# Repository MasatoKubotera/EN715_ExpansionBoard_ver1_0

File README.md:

<html lang="en">
  <head>
    <meta charset="uft-8">
    <meta name="author" content="Masato Kubotera">
  </head>
  <body>
    <h1>EN715 Expansion Board Ver. 1.0</h1>
    <h2>About EN715 Expansion Board</h2>
    <p>
      The EN715 Expansion Board is a circuit board to expand the functions of the Carrier Board for NVIDIA Jetson manufactured by AverMedia.<br>
      <br>
      Note that this is Ver. 1.0. For other versions, please refer to the following repositories.
      <ul>
        <li><a href="https://github.com/MasatoKubotera/EN715_ExpansionBoard_ver1_1">EN715 Expansion Board Ver. 1.1</a></li>
        <li><a href="https://github.com/MasatoKubotera/EN715_ExpansionBoard_ver1_2">EN715 Expansion Board Ver. 1.2</a></li>
      </ul>
      <h2>About Ver. 1.0</h2>
      Ver 1.0 was designed to facilitate the development of the AverMedia EN715 environment. As such, it is designed to support multiple communication methods.<br>
      Ver. 1.0 has the 2-port USB 2.0 Hi-Speed Hub on the board, which can be used by connecting an external USB Mini-B cable.<br>
      In addition, the MPU-9250 (9-Axis MotionTracking Device Module) module from Strawberry Linux can be installed, and SPI or I2C can be selected as the communication method via a short land on the board.<br>
      Additionally, two I2C (I2C0 and I2S1) ports and a UART (UART2) port with 3.3V signal can be connected via JST XH connector.<br>
      To install in the AverMedia EN715, connect the pin socket to the EN715's "20-pin Expansion header" and secure using 13mm length M3 spacers (e.g. <a href="http://www.hirosugi.jp/products/A/ASL-BE.html">ASL-313BE</a>).<br><br>
      This version was intended for development purposes and was never installed and used on a real robot.
      <!--
      Ver1.0は，AverMedia EN715の環境整備を促進するために設計されました．そのため，複数の通信方式に対応できるように設計されています．
      Ver.1.1 では，基板上に4ポートのUSB 2.0 Hi-Speed Hubを搭載しており，外付けのUSB Mini-Bケーブルを接続することでことで利用できます．
      また，Strawberry Linux 社の MPU-9250 (9-Axis MotionTracking Device Module) モジュールを装着することができ，基板上のショートランドにより，通信方式としてSPIかI2Cを選択することができます．
      さらに，2つのI2C（I2C0とI2S1）ポートと3.3V信号のUART (UART2)ポートをJST XHコネクタで接続することが可能です．
      AverMedia EN715に取り付けるには，ピンソケットをEN715の「20pin Expansion header」に接続し，13mm長のM3スペーサー（例：ASL-313BE）で固定します．
      このバージョンは開発用で，実際のロボットにインストールされて使用されたことはありません．
      -->
      <table>
        <tr>
          <td>
            <a href="image/brd_bottom.png">
              <div align="center">
                
              </div>
            </a>
          </td>
          <td>
            <div align="center">
              
            </div>
          </td>
        </tr>
        <tr>
          <td>
            <div align="center">
              PCB preview image
            </div>
          </td>
          <td>
            <div align="center">
              After component mounting
            </div>
          </td>    
        </tr>
      </table>
    </p>
    <h2>Repository Contents</h2>
    <p>
    <dl>
      <dt>\image</dt>
      <dd>PCB preview images and capture of design screen</dd>
      <dt>\libraries</dt>
      <dd>Libraries used in Autodesk Eagle design</dd>
      <dt>Schematic.pdf</dt>
      <dd>Circuit diagram of this product</dd>
      <dt>BOM.txt</dt>
      <dd>Parts lists output from design data</dd>
      <dt>.brd</dt>
      <dd>Board wiring design file by Autodesk Eagle</dd>
      <dt>.sch</dt>
      <dd>Schematic design file by Autodesk Eagle</dd>
      <dt>Gerber_data.zip</dt>
      <dd>Zip folder of Gerber format files for PCB manufacturing requests.</dd>
      <dt>LICENSE</dt>
      <dd>This is a license to use this product. Please confirm before use.</dd>
      <dt>.gitignore</dt>
      <dd>File to exclude cache files from management.</dd>
    </dl>
    </p>
    <h2>Documentation</h2>
      <p>
        <h3>BOM</h3>
          <table>
            <thead>
              <tr>
                <th> Eagle Design Parts # </th>
                <th> Q'ty </th>
                <th> Mfr. Product # </th>
                <th> Supplier </th>
                <th> Description </th>
              </tr>
            </thead>
            <tbody>
              <tr>
                <td> C1, C2, C3 </td>
                <td> 3 </td>
                <td> GRM188R6YA106MA73 </td>
                <td> <a href="https://akizukidenshi.com/catalog/g/gP-13161/">Akizuki</a> </td>
                <td> Multilayer Ceramic Capacitors SMD/SMT 10uF 35V 20% 0603 </td>
              </tr>
              <tr>
                <td> C4 </td>
                <td> 1 </td>
                <td> GRM188B11H103KA01 </td>
                <td> <a href="https://akizukidenshi.com/catalog/g/gP-13387/">Akizuki</a> </td>
                <td> Multilayer Ceramic Capacitors SMD/SMT 0.01uF 50V 10% 0603 </td>
              </tr>
              <tr>
                <td> C5, C6 </td>
                <td> 2 </td>
                <td> C1608C0G1H220J080AA </td>
                <td> <a href="https://www.mouser.jp/ProductDetail/TDK/C1608C0G1H220J080AA?qs=NRhsANhppD%2FvEAPMU6eN6g%3D%3D">Mouser</a> </td>
                <td> Multilayer Ceramic Capacitors SMD/SMT 22pF 50V 5% 0603 </td>
              </tr>
              <tr>
                <td> CH1 </td>
                <td> 1 </td>
                <td> FH-2x10SG </td>
                <td> <a href="https://akizukidenshi.com/catalog/g/gC-00083/">Akizuki</a> </td>
                <td> 2.54mm Pin Socket, 2 Row, 20 Pin </td>
              </tr>
              <tr>
                <td> CH2, </td>
                <td> 1 </td>
                <td> S4B-XH-A(LF)(SN) </td>
                <td> <a href="https://www.daisen-netstore.com/shopdetail/000000000028/ct15/page1/order/">DAISEN</a> </td>
                <td> Connector Header Through Hole, Right Angle 4 position 2.54mm RED </td>
              </tr>
              <tr>
                <td> CH3 </td>
                <td> 1 </td>
                <td> S4B-XH-A(LF)(SN) </td>
                <td> <a href="https://www.daisen-netstore.com/shopdetail/000000000028/ct15/page1/order/">DAISEN</a> </td>
                <td> Connector Header Through Hole, Right Angle 4 position 2.54mm YELLOW </td>
              </tr>
              <tr>
                <td> CH4 </td>
                <td> 1 </td>
                <td> S4B-XH-A(LF)(SN) </td>
                <td> <a href="https://www.daisen-netstore.com/shopdetail/000000000028/ct15/page1/order/">DAISEN</a> </td>
                <td> Connector Header Through Hole, Right Angle 4 position 2.54mm BLUE </td>
              </tr>
              <tr>
                <td> CR1 </td>
                <td> 1 </td>
                <td> FA-238V 12.0000MB-K3 </td>
                <td> <a href="https://akizukidenshi.com/catalog/g/gP-05225/">Akizuki</a> </td>
                <td> Crystals 12.0000MHz 50ppm 10pF -40C +85C </td>
              </tr>
              <tr>
                <td> D1, D2, D3, D4, D5, D6 </td>
                <td> 6 </td>
                <td> CG0603MLC-05E </td>
                <td> <a href="https://www.mouser.jp/ProductDetail/Bourns/CG0603MLC-05E?qs=lDok7oSghXVLNKMK69q%252BFQ%3D%3D">Mouser</a> </td>
                <td> ESD Protectors 5V 0603 </td>
              </tr>
              <tr>
                <td> F1 </td>
                <td> 1 </td>
                <td> MF-MSMF050-2 </td>
                <td> <a href="https://www.mouser.jp/ProductDetail/Bourns/MF-MSMF050-2?qs=t3shhpq1i1DZ7OBD5kLNoA%3D%3D">Mouser</a> </td>
                <td> PTC Resettable Fuses 15V .5A-HD 100A MAX </td>
              </tr>
              <tr>
                <td> FL1, FL2, FL3 </td>
                <td> 3 </td>
                <td> BLM18SD220SN1D </td>
                <td> <a href="https://www.mouser.jp/ProductDetail/Murata-Electronics/BLM18SD220SN1D?qs=glnLrWX4TPq%2Fm8%2FdPQltLg%3D%3D">Mouser</a> </td>
                <td> Ferrite Beads 22 OHM 0603 </td>
              </tr>
              <tr>
                <td> IC1 </td>
                <td> 1 </td>
                <td> FE1.1S </td>
                <td> <a href="https://www.aitendo.com/product/16185">aitendo</a> </td>
                <td> USB Interface IC USB 2.0 Hi-Speed 4 Port Hub Controller </td>
              </tr>
              <tr>
                <td> LED1 </td>
                <td> 1 </td>
                <td> 150060VS86000 </td>
                <td> <a href="https://www.mouser.jp/ProductDetail/Wurth-Elektronik/150060VS86000?qs=GedFDFLaBXGW9qOjzZ1Hmw%3D%3D">Mouser</a> </td>
                <td> Standard LEDs - SMD Green 2V 20mA 573nm 0603 </td>
              </tr>
              <tr>
                <td> LED2,LED3,LED4 </td>
                <td> 3 </td>
                <td> 150060YS75000 </td>
                <td> <a href="https://www.mouser.jp/ProductDetail/Wurth-Elektronik/150060YS75000?qs=LlUlMxKIyB0nKmwefHgtZw%3D%3D">Mouser</a> </td>
                <td> Standard LEDs - SMD Yellow 2V 20mA 590nm 0603 </td>
              </tr>
              <tr>
                <td> M1 </td>
                <td> 1 </td>
                <td> MPU-9250 Module </td>
                <td> <a href="https://strawberry-linux.com/catalog/items?code=12250">Strawberry Linux</a> </td>
                <td> 9-Axis MotionTracking Device Module </td>
              </tr>
              <tr>
                <td> M1 </td>
                <td> 1 </td>
                <td> 6604S-40 </td>
                <td> <a href="https://akizukidenshi.com/catalog/g/gP-01591/">Akizuki</a> </td>
                <td> 2.54mm Pin Socket Strip, Single Row </td>
              </tr>
              <tr>
                <td> M1 </td>
                <td> 1 </td>
                <td> PHA-1x40SG </td>
                <td> <a href="https://akizukidenshi.com/catalog/g/gC-06631/">Akizuki</a> </td>
                <td> 2.54mm Pin Header Strip, Straight, Single Row </td>
              </tr>
              <tr>
                <td> R1, R3, R4, R5 </td>
                <td> 4 </td>
                <td> RC0603FR-101KL </td>
                <td> <a href="https://www.mouser.jp/ProductDetail/YAGEO/RC0603FR-101KL?qs=EiqXWrxQq63MM0wzm69ZKg%3D%3D">Mouser</a> </td>
                <td> Thick Film Resistors - SMD 1 kOhms 100-200mW 1% 0603 </td>
              </tr>
              <tr>
                <td> R2 </td>
                <td> 1 </td>
                <td> RC0603FR-102K7L </td>
                <td> <a href="https://www.mouser.jp/ProductDetail/YAGEO/RC0603FR-102K7L?qs=Iqe6t0HYRD6Xaw3IgOqXnw%3D%3D">Mouser</a> </td>
                <td> Thick Film Resistors - SMD 2.7 kOhms 100-200 mW 1% 0603 </td>
              </tr>
              <tr>
                <td> USB1 </td>
                <td> 1 </td>
                <td> MUSB-5B-NE-S175 </td>
                <td> <a href="https://akizukidenshi.com/catalog/g/gC-05843/">Akizuki</a> </td>
                <td> Mini USB Connector 5P B type, Female, SMT type, without standoff </td>
              </tr>
              <tr>
                <td> USB2, USB3 </td>
                <td> 2 </td>
                <td> USB1046-GF-0190-L-B-A </td>
                <td> <a href="https://www.mouser.jp/ProductDetail/640-USB1046GF0190LBA">Mouser</a> </td>
                <td> USB Connectors USB2.0 A, Top Mount, SMT </td>
              </tr>
            </tbody>
          </table>         
        <h3>PCB Fabrication</h3>
          PCB(Printed Circuit Board) manufacturing was outsourced to <a href="https://www.elecrow.com/pcb-manufacturing.html">Elecrow</a>.<br>
          The custom specifications are as follows.
          <ul>
            <li>Layer : 2 layers</li>
            <li>Dimensions : 87 x 50</li>
            <li>PCB Qty : 10</li>
            <li>Different PCB Design : 1eg</li>
            <li>PCB Thickness : 1.6</li>
            <li>PCB Color : Black</li>
            <li>Surface Finish : HASL Lead Free</li>
            <li>Castellated Hole : No</li>
            <li>Copper Weight : 1oz</li>
            <li>PCB Stencil : Stencil 15cm X 15cm no frame</li>
          </ul>
          The data used to order fabrication are as follows.
          <ul>
            <li>Eagle design rule : <a href="https://www.elecrow.com/download/Elecrow_PCB_eagle_rule.zip">Elecrow Eagle Design Rule</a></li>
            <li>Eagle CAM file : <a href="https://www.elecrow.com/download/Elecrow_Gerber_Generater_DrillAlign.zip">Elecrow CAM file</a></li>
            <li>Gerber format data : <a href="/Gerber_data.zip">Gerber_data.zip</a></li>
          </ul>
      </p>
    <h2>Contact</h2>
    <p>
    If you have any questions, please contact MasatoKubotera, the product's designer, by E-mail.<br>
    E-mail : <a href="mailto:masatokubotera06@yahoo.co.jp">masatokubotera06@yahoo.co.jp</a>
    </p>
    <h2>License Information</h2>
    <p>
      This product is open source.<br>
      Please review the <a href="/LICENSE">LICENSE file</a> for license information.<br>
      <br>
      <strong>EN715 Expansion Board Ver. 1.0</strong> by Masato Kubotera is licensed under a <a href="http://creativecommons.org/licenses/by-nc-sa/4.0/">Creative Commons Attribution-NonCommercial-ShareAlike 4.0 International License</a>.
    </p>    
  </body>
</html>

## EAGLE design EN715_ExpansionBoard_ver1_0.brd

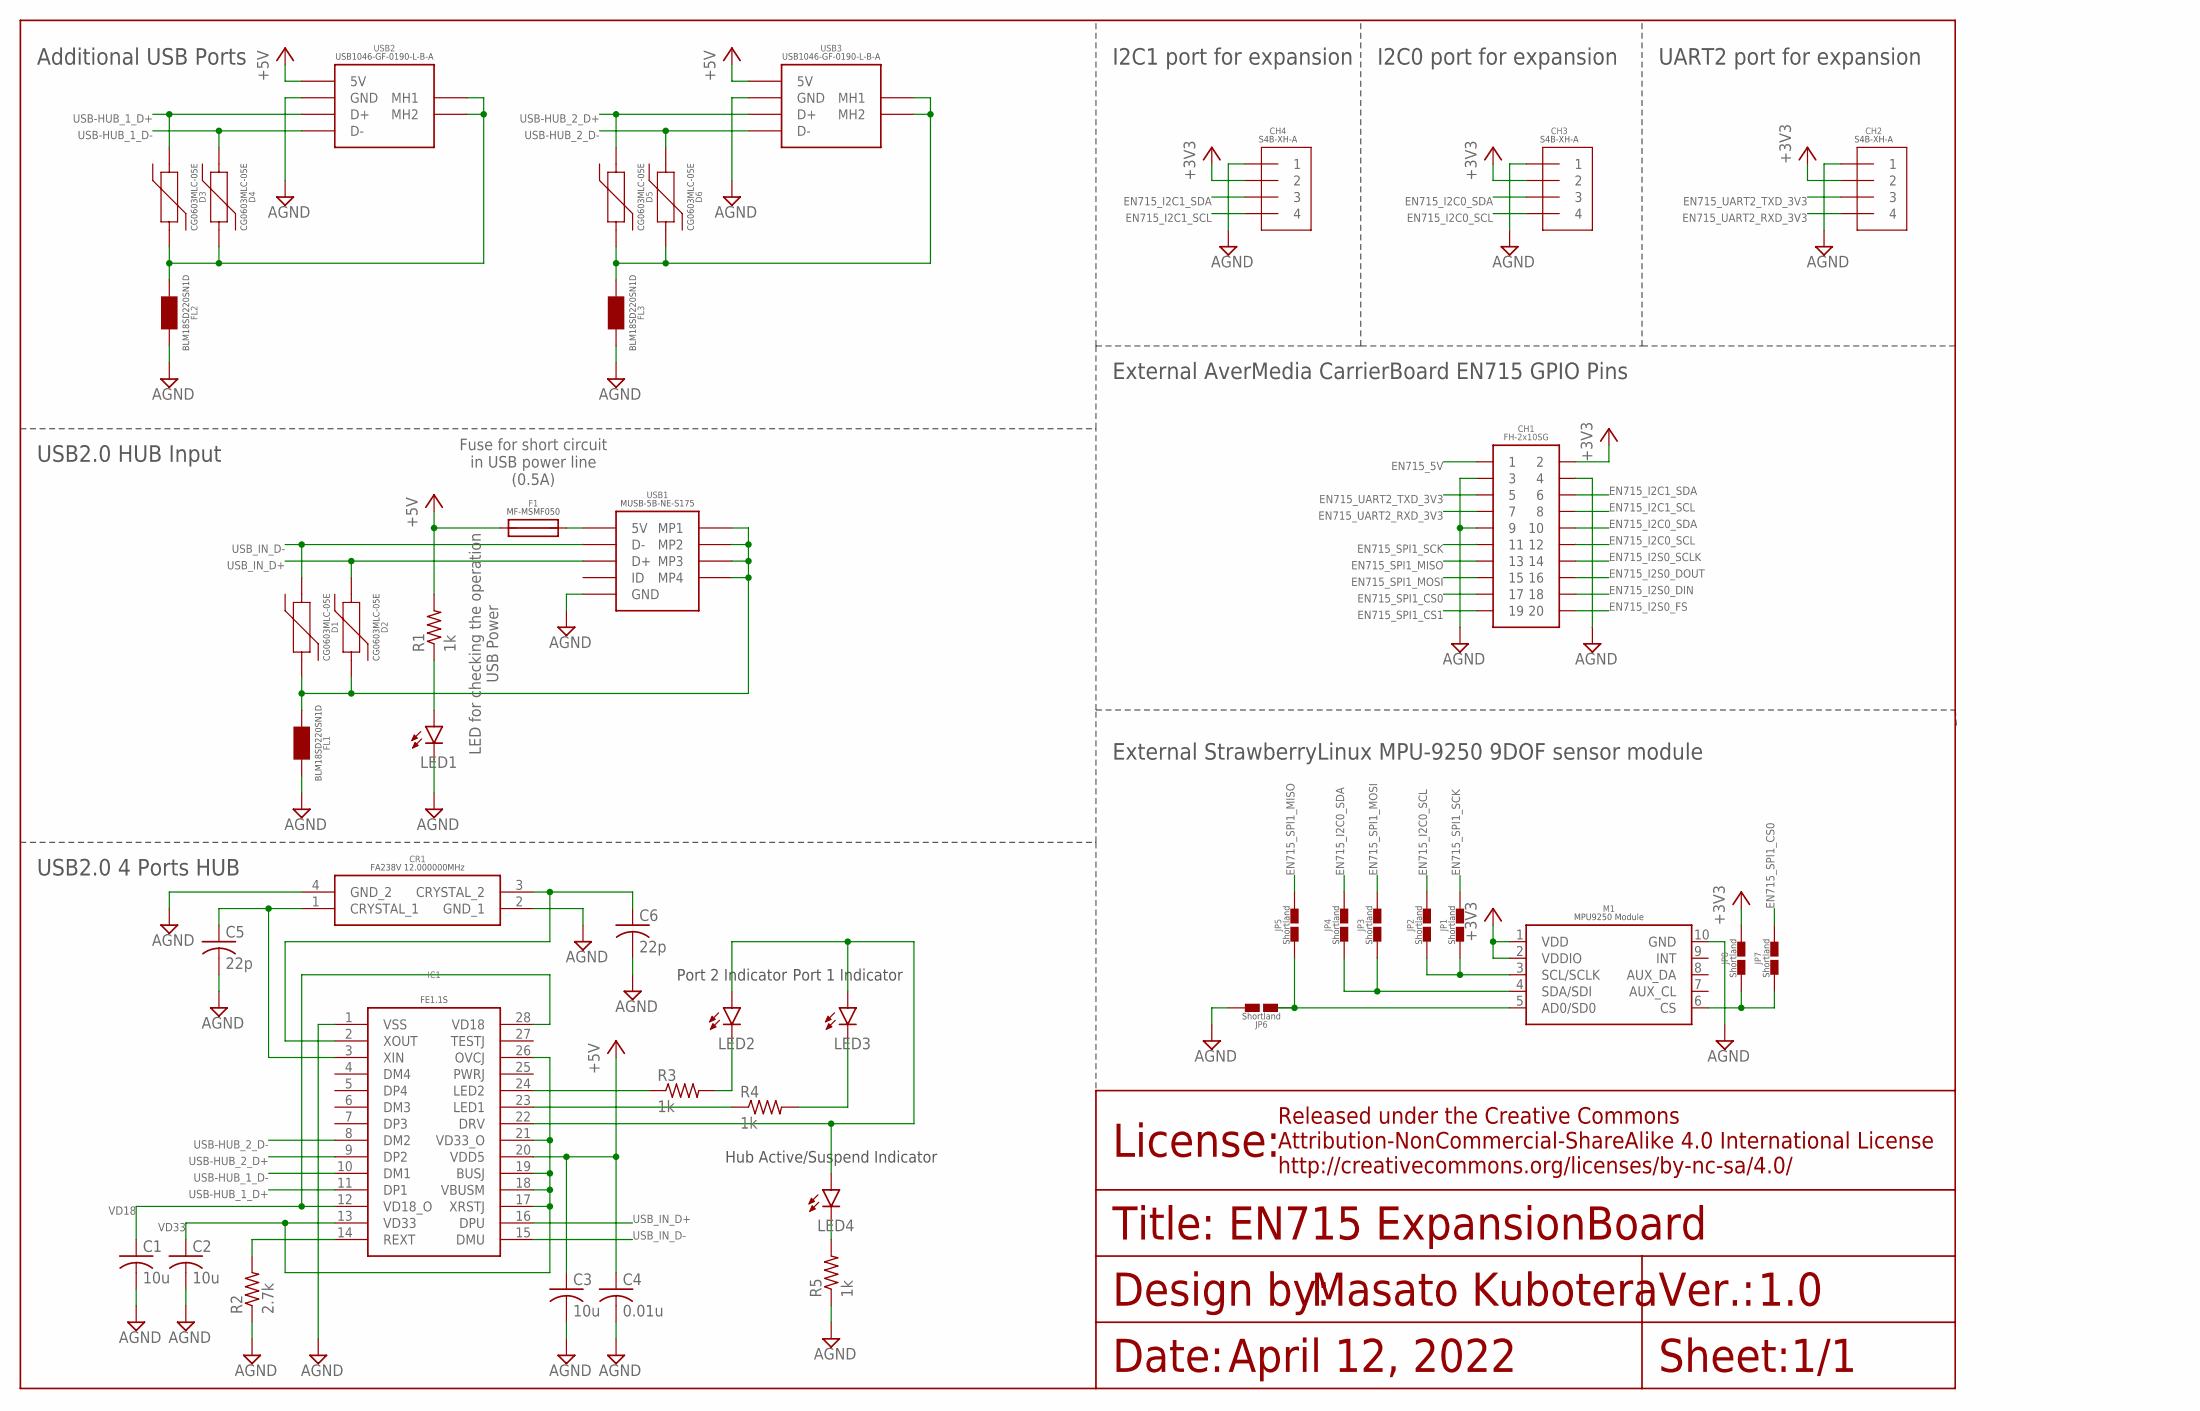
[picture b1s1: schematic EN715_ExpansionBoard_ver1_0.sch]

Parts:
C1, C2, C3: 10u; C0603
C4: 0.01u; C0603
C5, C6: 22p; C0603
CH1: 2X10
CH2, CH3, CH4: S4B-XH-A
CR1: FA238V_12.000000MHZ; FA238V
D1, D2, D3, D4, D5, D6: CG0603MLC-05E
F1: MF-MSMF050
FL1, FL2, FL3: BLM18SD220SN1D
IC1: FE1.1S
JP1, JP2, JP3, JP4, JP5, JP6, JP7, JP8: SHORTLAND
LED1, LED2, LED3, LED4: LEDSML0603; SML0603
M1: MPU9250_MODULE
R1, R3, R4, R5: 1k; R0603
R2: 2.7k; R0603
USB1: MINI_USB_B_SMD
USB2, USB3: USB_A_X1_SMD

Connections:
+3V3: CH1.2, CH2.2, CH3.2, CH4.2, JP8.2, M1.1 (VDD), M1.2 (VDDIO)
+5V: C3.1, C4.1, F1.1, IC1.20 (VDD5), R1.2, USB2.1 (5V), USB3.1 (5V)
AGND: C1.2, C2.2, C3.2, C4.2, C5.2, C6.2, CH1.3, CH1.4, CH1.9, CH2.1, CH3.1, CH4.1, CR1.2 (GND_1), CR1.4 (GND_2), FL1.2, FL2.2, FL3.2, IC1.1 (VSS), JP6.2, LED1.C, M1.10 (GND), R2.1, R5.1, USB1.5 (GND), USB2.4 (GND), USB3.4 (GND)
B_FUSE_USB_MINI_B: F1.2, USB1.1 (5V)
EN715_5V: CH1.1
EN715_I2C0_SCL: CH1.12, CH3.4, JP2.2
EN715_I2C0_SDA: CH1.10, CH3.3, JP4.2
EN715_I2C1_SCL: CH1.8, CH4.4
EN715_I2C1_SDA: CH1.6, CH4.3
EN715_I2S0_DIN: CH1.18
EN715_I2S0_DOUT: CH1.16
EN715_I2S0_FS: CH1.20
EN715_I2S0_SCLK: CH1.14
EN715_SPI1_CS0: CH1.17, JP7.2
EN715_SPI1_CS1: CH1.19
EN715_SPI1_MISO: CH1.13, JP5.2
EN715_SPI1_MOSI: CH1.15, JP3.2
EN715_SPI1_SCK: CH1.11, JP1.2
EN715_UART2_RXD_3V3: CH1.7, CH2.4
EN715_UART2_TXD_3V3: CH1.5, CH2.3
FE1.1S_DRV: IC1.22 (DRV), LED2.A, LED3.A, LED4.A
FE1.1S_DRV_LED_A: LED4.C, R5.2
FE1.1S_LED1_A: LED3.C, R4.2
FE1.1S_LED_1_B: IC1.23 (LED1), R4.1
FE1.1S_LED_2_A: LED2.C, R3.2
FE1.1S_LED_2_B: IC1.24 (LED2), R3.1
LED_USBIN: LED1.A, R1.1
MPU9250_AD0/SD0: JP5.1, JP6.1, M1.5 (AD0/SD0)
MPU9250_CS: JP7.1, JP8.1, M1.6 (CS)
MPU9250_SCL/SCLK: JP1.1, JP2.1, M1.3 (SCL/SCLK)
MPU9250_SDA/SDI: JP3.1, JP4.1, M1.4 (SDA/SDI)
REXT_FE1.1S: IC1.14 (REXT), R2.2
USB-HUB_1_D+: D3.1, IC1.11 (DP1), USB2.3 (D+)
USB-HUB_1_D-: D4.1, IC1.10 (DM1), USB2.2 (D-)
USB-HUB_2_D+: D5.1, IC1.9 (DP2), USB3.3 (D+)
USB-HUB_2_D-: D6.1, IC1.8 (DM2), USB3.2 (D-)
USB_A_1_SHIELD: D3.2, D4.2, FL2.1, USB2.MH1, USB2.MH2
USB_A_2_SHIELD: D5.2, D6.2, FL3.1, USB3.MH1, USB3.MH2
USB_IN_D+: D2.1, IC1.16 (DPU), USB1.3 (D+)
USB_IN_D-: D1.1, IC1.15 (DMU), USB1.2 (D-)
USB_MINI_B_SHIELD: D1.2, D2.2, FL1.1, USB1.MP1, USB1.MP2, USB1.MP3, USB1.MP4
VD18: C1.1, IC1.12 (VD18_O), IC1.28 (VD18)
VD33: C2.1, IC1.13 (VD33), IC1.17 (XRSTJ), IC1.18 (VBUSM), IC1.19 (BUSJ), IC1.21 (VD33_O), IC1.26 (OVCJ)
XIN_FE1.1S: C5.1, CR1.1 (CRYSTAL_1), IC1.3 (XIN)
XOUT_FE1.1S: C6.1, CR1.3 (CRYSTAL_2), IC1.2 (XOUT)

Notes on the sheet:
Hub Active/Suspend Indicator
Port 1 Indicator
Port 2 Indicator
Fuse for short circuit in USB power line (0.5A)
LED for checking the operation USB Power
EN715 ExpansionBoard
1.0
1/1
USB2.0 4 Ports HUB
Additional USB Ports
External StrawberryLinux MPU-9250 9DOF sensor module
USB2.0 HUB Input
April 12, 2022
External AverMedia CarrierBoard EN715 GPIO Pins
I2C1 port for expansion
I2C0 port for expansion
UART2 port for expansion

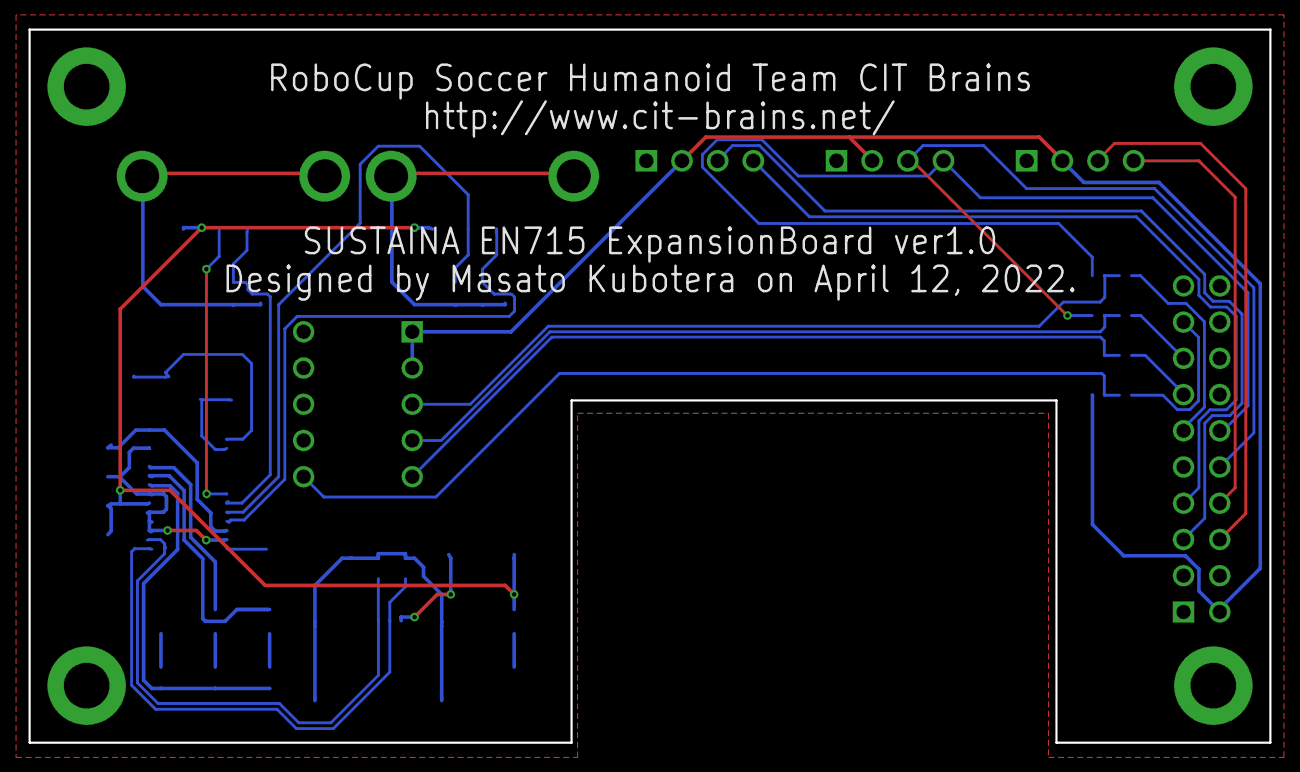
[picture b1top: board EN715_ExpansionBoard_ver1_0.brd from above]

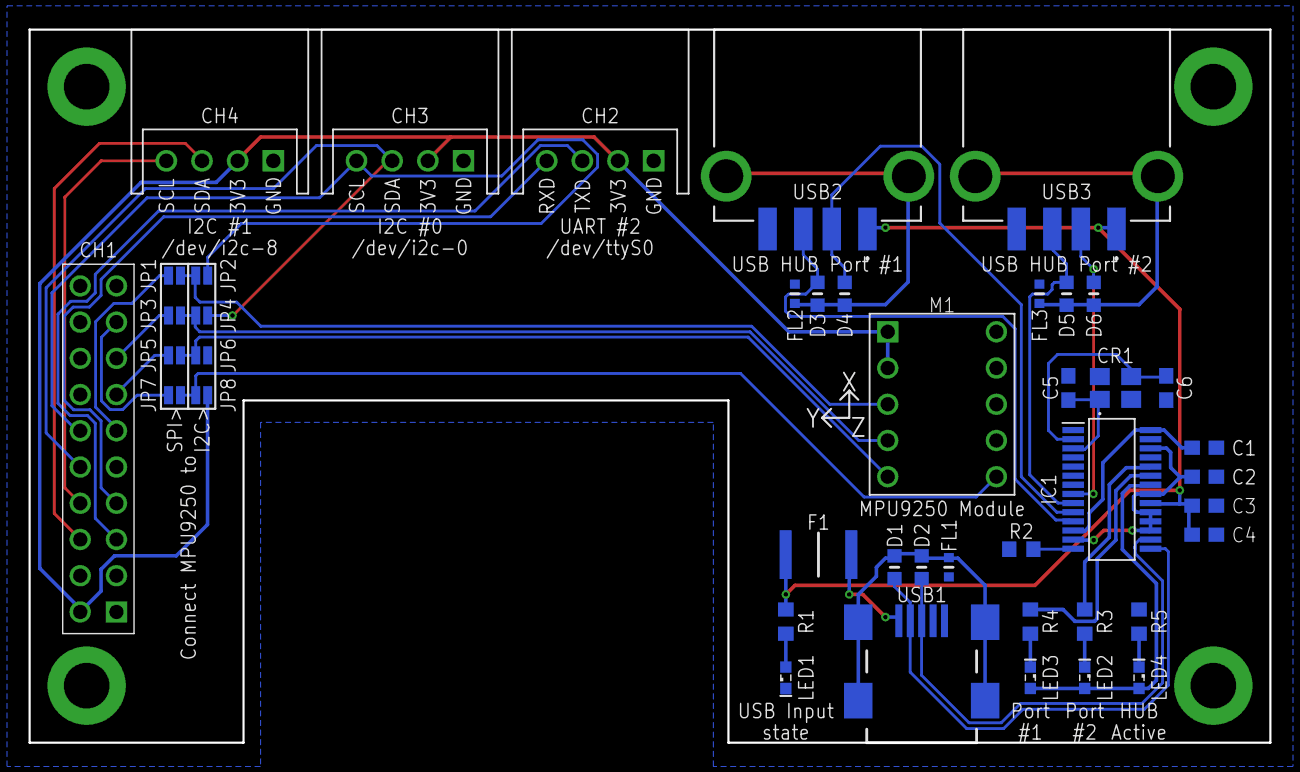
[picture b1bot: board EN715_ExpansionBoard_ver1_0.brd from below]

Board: 2 copper layers, 87.0 x 50.0 mm, 43 parts (43 on the bottom side), 39 nets.

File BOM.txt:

Partlist exported from C:/Users/Masato/Documents/citbrains/EN715_ExpansionBoard_ver1_0/EN715_ExpansionBoard_ver1_0.sch at 2022/09/21 2:35

Qty Value               Device              Package        Parts                                  Description                
4                       LEDSML0603          SML0603        LED1, LED2, LED3, LED4                 LED                        
1   0.01u               C-USC0603           C0603          C4                                     CAPACITOR, American symbol 
3   10u                 C-USC0603           C0603          C1, C2, C3                             CAPACITOR, American symbol 
4   1k                  R-US_R0603          R0603          R1, R3, R4, R5                         RESISTOR, American symbol  
1   2.7k                R-US_R0603          R0603          R2                                     RESISTOR, American symbol  
2   22p                 C-USC0603           C0603          C5, C6                                 CAPACITOR, American symbol 
1   2X10                2X10                2X10           CH1                                                               
3   BLM18SD220SN1D      BLM18SD220SN1D      BLM18SD220SN1D FL1, FL2, FL3                                                     
6   CG0603MLC-05E       CG0603MLC-05E       CG0603MLC-05E  D1, D2, D3, D4, D5, D6                                            
1   FA238V_12.000000MHZ FA238V_12.000000MHZ FA238V         CR1                                                               
1   FE1.1S              FE1.1S              FE1.1S         IC1                                                               
1   MF-MSMF050          MF-MSMF050          MF-MSMF050     F1                                                                
1   MINI_USB_B_SMD      MINI_USB_B_SMD      MINI_USB_B_SMD USB1                                                              
1   MPU9250_MODULE      MPU9250_MODULE      MPU9250_MODULE M1                                                                
3   S4B-XH-A            S4B-XH-A            S4B-XH-A       CH2, CH3, CH4                                                     
8   SHORTLAND           SHORTLAND           SHORTLAND      JP1, JP2, JP3, JP4, JP5, JP6, JP7, JP8                            
2   USB_A_X1_SMD        USB_A_X1_SMD        USB_A_X1_SMD   USB2, USB3

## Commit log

2022-09-20 Initial upload of data
2022-09-23 Update LICENSE

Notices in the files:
parts and their libraries:
Frame: Released under the Creative Commons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
